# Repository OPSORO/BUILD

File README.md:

# OPSORO BUILD
Mechanical components of the OPSORO system.

Files are organized as follows:
- modules — Design files of all grid-compatible modules
- grid — Grids and grid-related accessories
- embodiments — Design files for robot embodiments
- accessories — Everything else.

Non-essential parts, including derived files (e.g. STL, DXF, AI), can be found in the extras/ folder of the parent directory.

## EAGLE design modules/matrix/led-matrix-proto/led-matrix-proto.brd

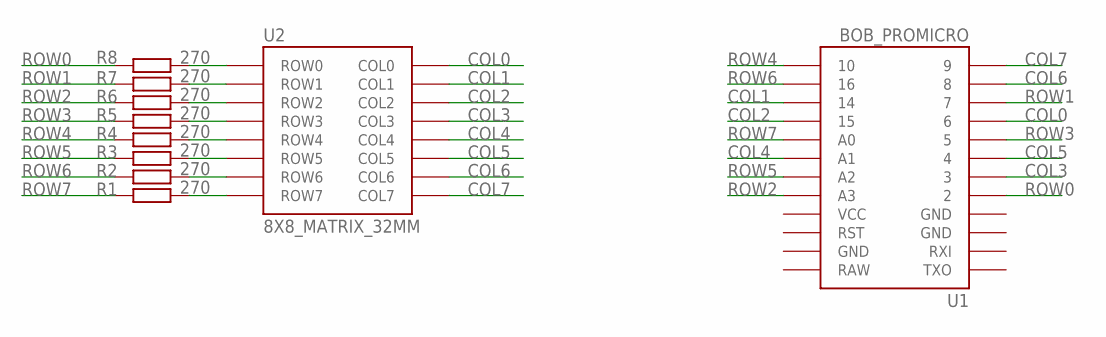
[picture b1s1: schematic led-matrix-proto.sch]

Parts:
R1, R2, R3, R4, R5, R6, R7, R8: 270; R0603
U1: BOB_PROMICRO
U2: 8X8_MATRIX_32MM

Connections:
COL0: U1.6, U2.4 (COL0)
COL1: U1.14, U2.14 (COL1)
COL2: U1.15, U2.13 (COL2)
COL3: U1.3, U2.7 (COL3)
COL4: U1.A1, U2.11 (COL4)
COL5: U1.4, U2.6 (COL5)
COL6: U1.8, U2.2 (COL6)
COL7: U1.9, U2.1 (COL7)
unnamed: R1.2, U2.12 (ROW7)
unnamed: R2.2, U2.15 (ROW6)
unnamed: R3.2, U2.10 (ROW5)
unnamed: R4.2, U2.16 (ROW4)
unnamed: R5.2, U2.5 (ROW3)
unnamed: R6.2, U2.9 (ROW2)
unnamed: R7.2, U2.3 (ROW1)
unnamed: R8.2, U2.8 (ROW0)
ROW0: R8.1, U1.2
ROW1: R7.1, U1.7
ROW2: R6.1, U1.A3
ROW3: R5.1, U1.5
ROW4: R4.1, U1.10
ROW5: R3.1, U1.A2
ROW6: R2.1, U1.16
ROW7: R1.1, U1.A0

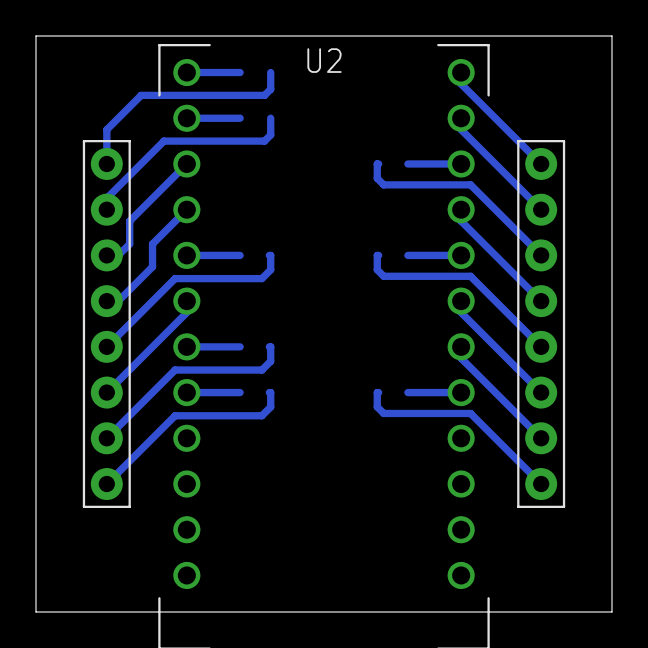
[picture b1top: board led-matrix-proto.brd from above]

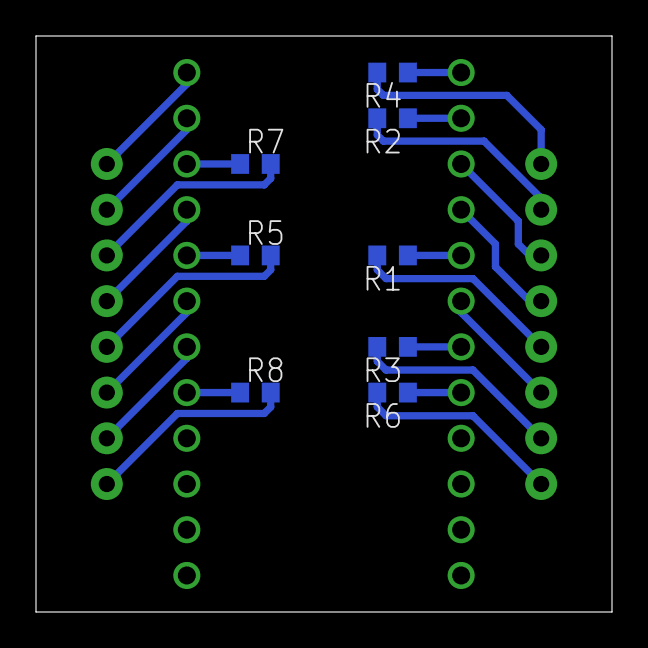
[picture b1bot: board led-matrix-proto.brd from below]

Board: 2 copper layers, 32.0 x 32.0 mm, 10 parts (8 on the bottom side), 24 nets.

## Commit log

2016-09-20 Initial files
2016-09-20 Resizing & labels
2016-09-20 Eye-link bend template
2016-09-21 Speaker & 3D-eye+ Bolt in clip system & fixes
2016-09-21 USB-Ethernet position
2016-10-14 Cleanup
2016-10-14 Eye update
2016-11-03 OPSORO A4 Grid System
2017-03-30 Reorganized folder structure. Added invader, matrix, button.
2017-03-30 Repo fix caps part1
2017-03-30 Repo fix caps part2
2017-04-07 Added camera module
2017-04-07 Camera module nibs adjusted
2017-04-07 Updated turn to support 90° orientation
2017-04-10 PIR motion module added
2017-04-21 Fixed duplicate edges
2017-04-21 Added 3D STEPs of laser-cut parts
2017-05-05 New LED matrix module
2017-06-08 Added keychain files
2017-06-08 Added stickers for button remote
2017-06-08 Generated STEPs for all modules
2017-06-09 SVG skin of Opsoro Invader
2017-06-09 Updated Invader skin with artboards
2017-06-16 Added initial version of eight-eyes
2017-06-16 Initial version of cardboard logo
2017-06-16 Invader skin SVG update
2017-06-16 Initial version of flat cardboard packaging
2017-06-16 Initial design of Kortrijk Kiosk
2017-06-29 Eight eyes design update
2017-06-29 Cardboard logo fabrication files
2017-07-13 Final Kiosk files
2017-08-23 Updated camera module so that camera is positioned right-side up
2017-08-23 Grid 3D model
2017-08-23 Added template for new modules
2017-08-28 Updated heart module to account for straight headers
